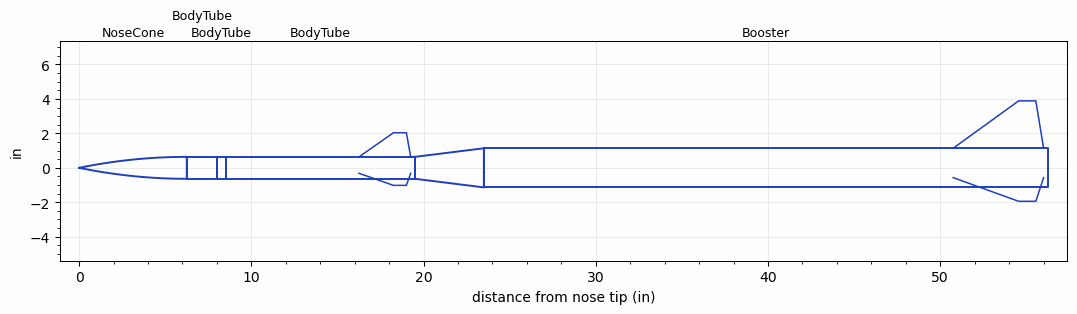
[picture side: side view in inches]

<RASAeroDocument>
 <FileVersion>2</FileVersion>
 <RocketDesign>
  <NoseCone>
   <Length>6.25</Length>
   <Diameter>1.274</Diameter>
   <Shape>Tangent Ogive</Shape>
   <Location>0</Location>
  </NoseCone>
  <BodyTube>
   <Length>1.75</Length>
   <Diameter>1.274</Diameter>
   <Location>6.25</Location>
  </BodyTube>
  <BodyTube>
   <Length>0.5</Length>
   <Diameter>1.274</Diameter>
   <Location>8</Location>
  </BodyTube>
  <BodyTube>
   <Length>11</Length>
   <Diameter>1.274</Diameter>
   <Location>8.5</Location>
   <Fin>
    <Count>3</Count>
    <Chord>3</Chord>
    <Span>1.4</Span>
    <SweepDistance>2</SweepDistance>
    <TipChord>0.75</TipChord>
    <Thickness>0.125</Thickness>
    <Location>3.25</Location>
    <AirfoilSection>Square</AirfoilSection>
   </Fin>
  </BodyTube>
  <Booster>
   <Length>32.7499</Length>
   <Diameter>2.274</Diameter>
   <InsideDiameter>1.274</InsideDiameter>
   <Location>19.5</Location>
   <ShoulderLength>4</ShoulderLength>
   <Fin>
    <Count>3</Count>
    <Chord>5.25</Chord>
    <Span>2.75</Span>
    <SweepDistance>3.8</SweepDistance>
    <TipChord>1</TipChord>
    <Thickness>0.125</Thickness>
    <Location>5.5</Location>
    <AirfoilSection>Square</AirfoilSection>
   </Fin>
  </Booster>
  <Surface>Camouflage Paint</Surface>
  <ModifiedBarrowman>True</ModifiedBarrowman>
  <Turbulence>True</Turbulence>
  <UseBooster1>True</UseBooster1>
  <UseBooster2>False</UseBooster2>
 </RocketDesign>
 <LaunchSite>
  <Altitude>800</Altitude>
  <Pressure>29.0769</Pressure>
  <RodAngle>2</RodAngle>
  <RodLength>71.9999</RodLength>
  <Temperature>56.1471</Temperature>
  <WindSpeed>8</WindSpeed>
 </LaunchSite>
 <Recovery>
  <Altitude1>700</Altitude1>
  <Altitude2>656.168</Altitude2>
  <DeviceType1>Parachute</DeviceType1>
  <DeviceType2>Parachute</DeviceType2>
  <Event1>True</Event1>
  <Event2>True</Event2>
  <Size1>24</Size1>
  <Size2>18</Size2>
  <EventType1>Altitude</EventType1>
  <EventType2>Apogee</EventType2>
  <CD1>0.5</CD1>
  <CD2>0</CD2>
 </Recovery>
 <SimulationList>
  <Simulation>
   <SustainerEngine>Dart  (NoThrust)</SustainerEngine>
   <SustainerLaunchWt>1.12</SustainerLaunchWt>
   <SustainerCG>12.35</SustainerCG>
   <SustainerIgnitionDelay>0</SustainerIgnitionDelay>
   <Booster1Engine>J540R  (AT)</Booster1Engine>
   <Booster1LaunchWt>5.34</Booster1LaunchWt>
   <Booster1SeparationDelay>0</Booster1SeparationDelay>
   <Booster1IgnitionDelay>0</Booster1IgnitionDelay>
   <Booster1CG>36.8</Booster1CG>
   <Booster1NozzleDiameter>1.25</Booster1NozzleDiameter>
   <IncludeBooster1>True</IncludeBooster1>
   <Booster2Delay>0</Booster2Delay>
   <IncludeBooster2>False</IncludeBooster2>
   <TimetoApogee>13.84017</TimetoApogee>
   <MaxAltitude>5256.808</MaxAltitude>
   <MaxVelocity>1120.621</MaxVelocity>
  </Simulation>
 </SimulationList>
</RASAeroDocument>
